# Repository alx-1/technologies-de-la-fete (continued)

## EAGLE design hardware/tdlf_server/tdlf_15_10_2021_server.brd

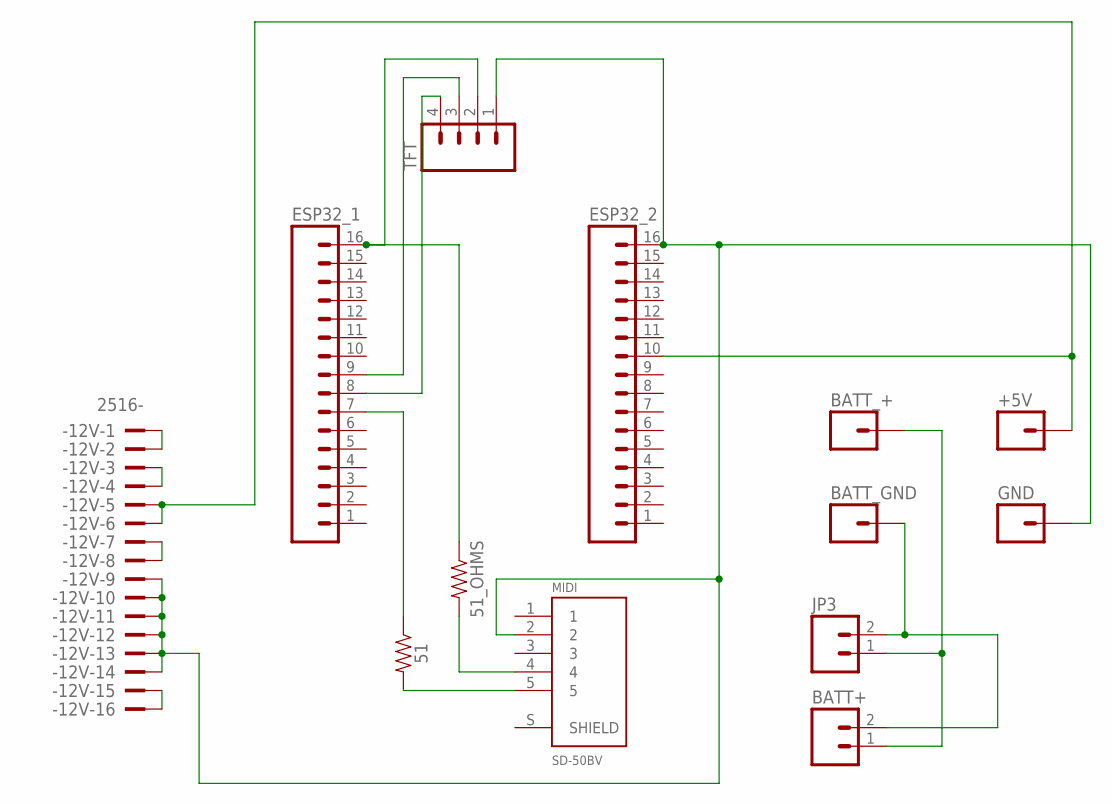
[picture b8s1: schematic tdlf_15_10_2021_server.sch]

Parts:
51, 51_OHMS: 1206
+5V: M01PTH; 1X01
-12V: 2516-; PAK100/2500-16
BATT+: M02PTH; 1X02
BATT_+: M01PTH; 1X01
BATT_GND: M01PTH; 1X01
ESP32_1, ESP32_2: M16PTH; 1X16
GND: M01PTH; 1X01
JP3: M02PTH; 1X02
MIDI: SD-50BV; CUI_SD-50BV
TFT: M04PTH; 1X04

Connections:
3V: 51_OHMS.2, MIDI.4
3V3: 51_OHMS.1, ESP32_1.16, TFT.2
5V: +5V.1, -12V.5, -12V.6, ESP32_2.10
+12V: -12V.7, -12V.8
+VBATT: BATT+.2, BATT_GND.1, JP3.2
-12V: -12V.15, -12V.16
GND: -12V.9, -12V.10, -12V.11, -12V.12, -12V.13, -12V.14, ESP32_2.16, GND.1, MIDI.2, TFT.1
GND_BATT: BATT+.1, BATT_+.1, JP3.1
unnamed: ESP32_1.9, TFT.3
unnamed: ESP32_1.8, TFT.4
unnamed: 51.1, ESP32_1.7
unnamed: -12V.1, -12V.2
unnamed: -12V.3, -12V.4
PIN27: 51.2, MIDI.5

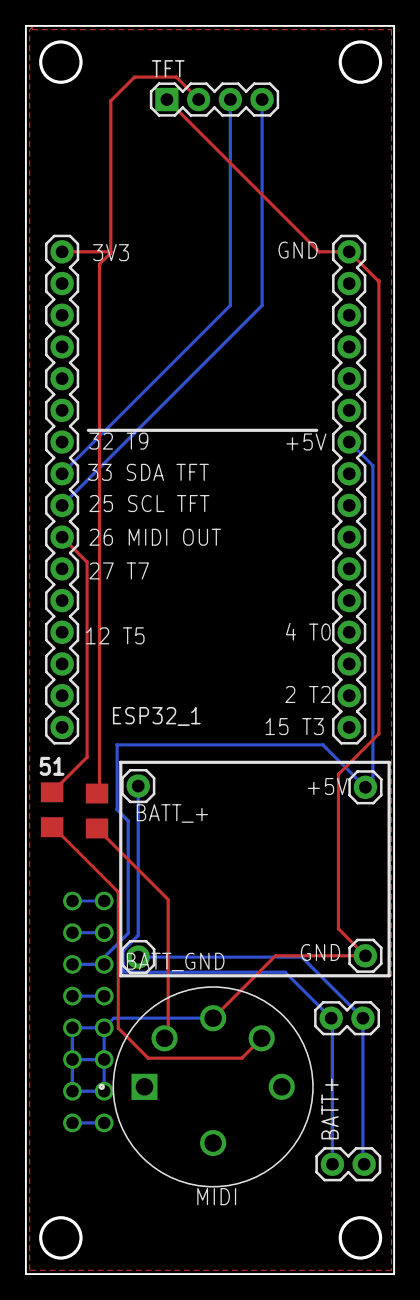
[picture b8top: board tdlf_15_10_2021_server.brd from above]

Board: 2 copper layers, 29.5 x 100.0 mm, 13 parts (1 on the bottom side), 14 nets.

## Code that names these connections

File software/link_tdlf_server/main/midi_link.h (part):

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        //if( MIDI_NOTES_DELAYED_OFF[i] > 0 && MIDI_NOTES_DELAYED_OFF[i] < monTemps ) {

        if( CV_TRIGGER_OFF[0] > 0 && CV_TRIGGER_OFF[0] < monTemps ) {
          gpio_set_level(CV_18, 0); // DAC_D // CV Trigger
          // gpio_set_level(CV_5, 0); // DAC_B // CV Clock Out
          // gpio_set_level(CV_23, 0); // DAC_C // CV Pitch
        }

        if( MIDI_NOTES_DELAYED_OFF[0] > 0 && MIDI_NOTES_DELAYED_OFF[0] < monTemps ) {
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                  // char zedata3[] = { MIDI_NOTE_VEL };
                  // uart_write_bytes(UART_NUM_1, zedata3, 1); // vélocité
                  
                  gpio_set_level(CV_18,1); // DAC_D (CV_18) get that note out !    
                  CV_TRIGGER_OFF[0] = int((esp_timer_get_time()/1000)+(myNoteDuration/64)); // set trigger duration
                }

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
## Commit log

2020-10-30 two boards for a capacitive touch based sequencer using the esp32 with ableton-link + hardware midi out
    The midi output is on the 'LED' board.
2020-10-30 images
    Showing the pinouts for the midi output
2020-10-30 pinouts ref for the TTGO esp32
    From espressif
2021-01-11 Touch + buttons
    Link with touchpads + buttons
2021-03-06 tdlf 0.1
    tdlf Server + client , Ableton live sequencer
2021-04-11 AbletonLive ESP32 with midi notes out
    broadcast for client detection and cfg
    LED feedback
    socket communication
    AbletonLink
    SmartWiFi for config
    new hardware board versions, separated the midi clock + notes out
2021-04-11 AbletonLink refactoring
    note data sent by sockets to the ESP32 based AbletonLive midi clock for added midi notes output
2021-04-11 ESP32 based AbletonLink enabled midi clock, midi data
    Sent via socket from the modular client
2021-04-11 adding folders
2021-04-11 link01
2021-04-11 ESP32 sequencer AbletonLive client for clock and midi out
2021-04-11 client README info
2021-04-11 Readme
    Correct link
2021-04-11 img server
2021-04-11 imgs
2021-04-11 images and dir name changes
2021-04-11 STEP file for the client module
2021-04-11 Demo video
    Will need to redo but it's a start
2021-04-11 STEP file now in hardware
2021-04-11 server files
2021-04-11 recreate tdlf server
2021-04-12 New LED library thanks to Leon Yuhanov
    https://github.com/leonyuhanov/ESP32APA102Driver
    TODO (done) Flicker LED[0],[4] and [5] are now working flawlessly.
2021-04-12 server code clean up
    Removing options for TTGO display
2021-04-12 better sync
    LEDs ok
    Offset solved
2021-04-13 Preparing for bar number and mute options
2021-04-13 Mute + bars
2021-04-14 mute && bars
    implemented
2021-04-17 NVS + smart config wifi handling, read in credentials at boot through nvs
    Smart config NVS enabled to set the wifi credentials from ESPTouch app if no IP is attributed
2021-04-18 Smart cfg, NVS
    Still errors with the client tasks initiating before getting an IP
2021-04-19 v 0.2 - udp Broadcast, ESPTouch, EVENT_STA_GOT_IP
    integration of the above in a coherent sequence of events
2021-04-19 moved LED init code, link + udp tasks indicate works
2021-04-20 new image for interface info
2021-04-21 Demo video
2021-04-22 Changes to vTaskDelays, step drift correction #1
2021-04-22 get current step from the session state...
    No more delays in the step count
2021-04-30 Better touch handling for the buttons
2021-05-17 node ableton link client for the ecosystem
    uses node-ableton from https://github.com/2bbb/node-abletonlink
    uses P5.js library touchgui https://github.com/L05/p5.touchgui
    thank you!
2021-05-18 node-abletonlink socket.io server + client
2021-05-18 recommitting node ableton link socket.io bridge
2021-05-21 changes to mtmss[] needed to use NVS
2021-05-21 Bump socket.io in /software/link_tdlf_webserver/tdlf_node-abletonlink
    Bumps [socket.io](https://github.com/socketio/socket.io) from 1.7.4 to 2.4.0.
    - [Release notes](https://github.com/socketio/socket.io/releases)
    - [Changelog](https://github.com/socketio/socket.io/blob/2.4.0/CHANGELOG.md)
    - [Commits](https://github.com/socketio/socket.io/compare/1.7.4...2.4.0)
2021-05-22 Added 3 touch pads for more options on the server hardware side
2021-08-17 wip
    new boards
    noteDuration
    tapTempo
2021-08-22 now with midi notes off for synth tracks
    midi notes off
    noteDuration
    long vs short touches detection
2021-08-22 New interface anim
2021-08-24 client IPs
    keep track of new client IPs
    update screen
2021-08-24 Create LICENSE
    About time ;)
2021-08-24 Update issue templates
2021-08-26 Sequence save and load
2021-08-26 New image of the tested v.03
    Modular form factor, a smaller standalone exists.
2021-09-04 Sequence saving and loading
    Save and load from NVS
    Keeps a list of the clients IP adresses
    Parse incoming client buffer for bar, note and step sequence
    More testing required
2021-09-12 Image for the smart config steps
2021-10-15 Clean up of tmp files produced by Eagle
2021-10-15 Further cleanup
2021-10-15 testing .gitignore
2021-10-23 hacklab21 + moving to CV outputs
2021-11-10 Moving to TRS for midi and three CV outputs
    For future use with physical interfaces sending sensor data via UDP to the server.
2021-11-17 Updates towards a web page
2021-11-19 Consigning code for getting ws events from Livepose
2021-12-05 Now with 3 CV outputs !
    Midi TRS out works
    CV out : the hardware works but the code needs to be implemented. Help needed :).
2021-12-05 Images of the new version
    With the cajita abierta wireless sensor interface !
    https://github.com/alx-1/CajitaAbierta
2021-12-08 Version 0.5 ready for CV outputs
2021-12-08 Adding the wireless sensor client to the main code
    It's called Cajita Abierta, it lets you :
    Connect any type of sensor, send data to the tdlf client through UDP. This is useful (tested for midi) for CC messages and expressive controls.
2021-12-24 CV Clock Out,
    CV Trigger works
    CV Clock Out - needs to be tested
    Update to socket.io 2.4.0
    Update node-abletonlink
2021-12-26 Updated BOM
2021-12-30 Operation diagrams
2022-01-01 Arduino code to set up a WAN on an ESP32
2022-01-01 tdlf ESP32 access point
    Image showing how to connect the tdlf to an ESP32 access point
2022-01-02 Testing CV Pitch out
2022-01-04 Software ENV updates
    Bumped to current ESP-IDF 4.3.2 and Ableton-link 3.0.3
    Refactored the file structure
    Adding CV Pitch output
2022-01-04 ESP32 dev setup options images
2022-01-05 CV Pitch Output works and tested
2022-01-06 CV_Clock out at 4 ticks per beat
2022-01-16 How to assemble the sensor (cajita abierta)
2022-01-21 New adjustments to the case model
2022-06-09 Now receiving osc midi messages
    Using tinyosc
2022-10-21 Ajouté(e) Diagramme sans nom.drawio
2022-10-21 banshees&&wizards
2022-10-24 Dusting 'in' - no real change
    Perhaps due to a change in OSX version...cmake creates new files. Did have to follow this for it to compile : https://esp32.com/viewtopic.php?t=16877
2022-10-24 Moving to OSC midi messages for the client
    Mostly removing low-level code that used to convert a bool array into sequencer data. OSC UDP communication between the client and server works.
2022-10-24 Forgot to remove the esp-osc test
    It served its purpose
2022-10-27 Moving towards a struct to keep track of sequence data
    Thank you https://github.com/maxdee!
    The array of structs keeps track of, note on/off, midiChannel, bar, note number, note length and mute info.
2022-10-27 Small changes to Bansheefy the client
    Not sending bar data (16 steps is ok if you only see one module at a time
    Not sending midi channel values - only one instrument -> the solenoids. Note numbers (0-7) are enough to distinguish between them.
2022-10-27 Starting to adapt the client to the new array of struct
    And receiving and parsing osc midi messages other than sensor data.
2022-10-29 Bump socket.io-parser and socket.io
    Bumps [socket.io-parser](https://github.com/socketio/socket.io-parser) to 4.2.1 and updates ancestor dependency [socket.io](https://github.com/socketio/socket.io). These dependencies need to be updat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
    Updates `socket.io-parser` from 2.3.1 to 4.2.1
    - [Release notes](https://github.com/socketio/socket.io-parser/releases)
    - [Changelog](https://github.com/socketio/socket.io-parser/blob/main/CHANGELOG.md)
    - [Commits](https://github.com/socketio/socket.io-parser/compare/2.3.1...4.2.1)
    Updates `socket.io` from 1.7.4 to 4.5.3
2022-10-29 remove build dir
2022-10-29 Moved sending the step to the 'if ( startstop )' section
    Sending step message through OSC
2022-10-29 Max's changes
2022-10-29 sequencer data is now stored in global state
2022-10-30 send sequence as string
2022-10-31 Petits changements
    Comments mostly
2022-10-31 remove more build files
2022-11-01 MVP 🎉
2022-11-01 output stored sequence upon receive
2022-11-03 Banshee-ification
    Assign the note number at the start, look for noteSelektor
2022-11-07 Refactoring the code into chunks
    "sockets.h"
    "i2c_display.h"
    "ledc.h"
    "touch_interactions.h"
    "mdns_wifi_cfg.h"
    "midi_link.h"
2022-11-20 A modular streamer for solenoids
    First attempt
2022-11-22 Bump engine.io and socket.io
    Bumps [engine.io](https://github.com/socketio/engine.io) to 6.2.1 and updates ancestor dependency [socket.io](https://github.com/socketio/socket.io). These dependencies need to be updated together.
    Updates `engine.io` from 1.8.5 to 6.2.1
    - [Release notes](https://github.com/socketio/engine.io/releases)
    - [Changelog](https://github.com/socketio/engine.io/blob/main/CHANGELOG.md)
    - [Commits](https://github.com/socketio/engine.io/compare/1.8.5...6.2.1)
    Updates `socket.io` from 1.7.4 to 4.5.3
2022-12-08 Bump qs and express
    Bumps [qs](https://github.com/ljharb/qs) to 6.11.0 and updates ancestor dependency [express](https://github.com/expressjs/express). These dependencies need to be updated together.
    Updates `qs` from 6.7.0 to 6.11.0
    - [Release notes](https://github.com/ljharb/qs/releases)
    - [Changelog](https://github.com/ljharb/qs/blob/main/CHANGELOG.md)
    - [Commits](https://github.com/ljharb/qs/compare/v6.7.0...v6.11.0)
    Updates `express` from 4.17.1 to 4.18.2
2022-12-14 Bump express in /software/link_tdlf_webserver/tdlf_node-abletonlink
    Bumps [express](https://github.com/expressjs/express) from 4.17.1 to 4.17.3.
    - [Release notes](https://github.com/expressjs/express/releases)
    - [Changelog](https://github.com/expressjs/express/blob/master/History.md)
    - [Commits](https://github.com/expressjs/express/compare/4.17.1...4.17.3)
    ---
    updated-dependencies:
2022-12-29 Moving to harmonize code for the blowsuck
    TFT screen functionalities
    UI for the config of CC messages
2023-01-22 Update tdlf_cajita_abierta_stick_v0.42.ino
    Accelerometer single + double tap
2023-01-22 tdlf cajita abierta, refactoring, captive portal
2023-02-23 Interface for the Cajita Abierta
    Commenting out some of the WT_32 specific code
    Re-enabling support for the Cajita Abierta
    Removing some printouts that speed up the reception of the OSC messages.
2023-05-29 Changes to the web app for the tdlf
2023-05-31 Scales and sequencer views show up ok
2023-06-12 functional abletonLink enabled javascript korg volca bass sequencer
2023-06-13 Updating socket.io to 4.6.2
2023-06-13 Start/stop enabled
2023-06-17 Update of all the clients when a sequence changes
2023-09-13 Sending osc data to Unity
2023-09-20 Preparing for UnityAbletonLink
2023-09-27 Cleanup of files from the node server
